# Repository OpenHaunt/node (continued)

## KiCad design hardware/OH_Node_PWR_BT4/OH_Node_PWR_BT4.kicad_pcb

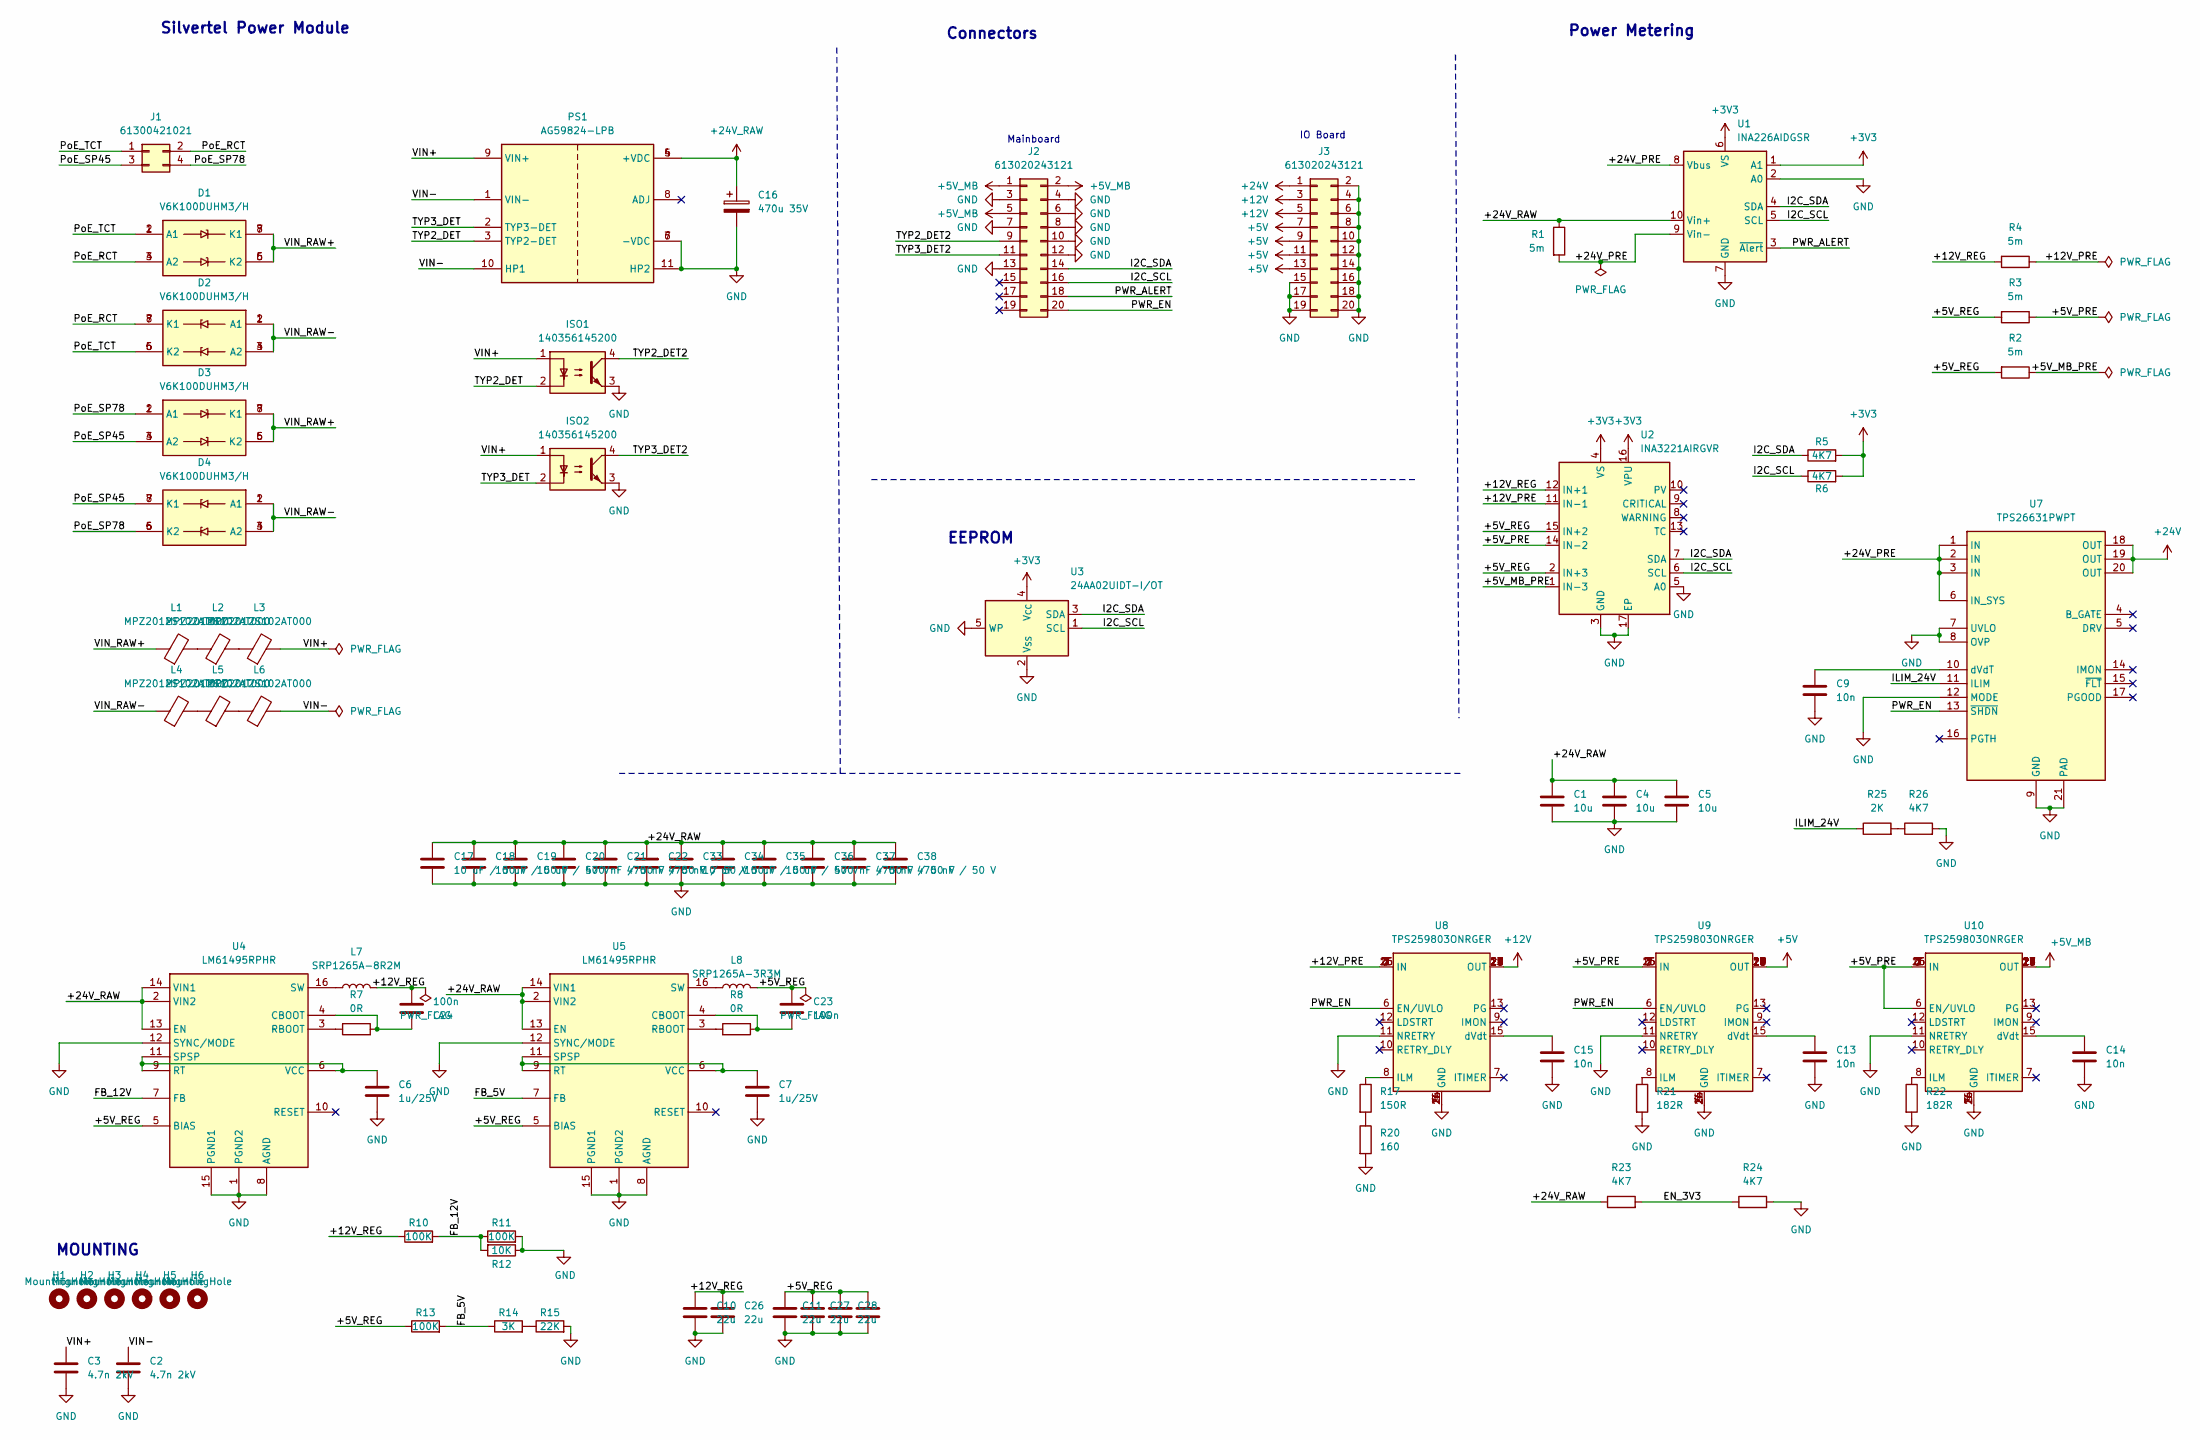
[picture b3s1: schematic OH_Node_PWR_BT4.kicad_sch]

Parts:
C1, C4, C5: 10u; C_0402_1005Metric; MPN GRM155R61A106ME11D
C2, C3: 4.7n 2kV; C_1812_4532Metric; MPN 885342211008
C6, C7: 1u/25V; C_0402_1005Metric; MPN CL05A105KA5NQNC
C9, C13, C14, C15: 10n; C_0402_1005Metric; MPN CL05B103KB5NNNC
C10, C11, C26, C27, C28, C29: 22u; C_1210_3225Metric; MPN GRM32ER71E226KE15L
C16: 470u 35V; CP_Elec_10x10.5; MPN EEH-ZU1V471P
C17, C18, C19, C33, C34, C35: 10 uF / 50 V; C_1210_3225Metric; MPN CC1210KKX7R9BB106
C20, C21, C22, C36, C37, C38: 470 nF / 50 V; C_0603_1608Metric; MPN C1608X7R1H474K080AC
C23, C24: 100n; C_0603_1608Metric; MPN CL10B104KB8NNNC
D1, D2, D3, D4: V6K100DUHM3/H; V6K100DUHM3H; Manufacturer_Part_Number V6K100DUHM3/H
H1, H2, H3, H4, H5, H6: MountingHole; MountingHole_2.7mm_M2.5_DIN965_Pad
ISO1, ISO2: 140356145200; WL-OCPT_SOP4; MPN 140356145200
J1: 61300421021; PinHeader_2x02_P2.54mm_Horizontal; MPN 61300421021
J2, J3: 613020243121; PinSocket_2x10_P2.54mm_Horizontal; MPN 613020243121
L1, L2, L3, L4, L5, L6: MPZ2012S102AT000; L_0805_2012Metric; MPN MPZ2012S102AT000
L7: SRP1265A-8R2M; Bourns_SRP1265A; MPN SRP1265A-8R2M
L8: SRP1265A-3R3M; Bourns_SRP1265A; MPN SRP1265A-3R3M
PS1: AG59824-LPB; AG59800-LPB; Manufacturer_Part_Number Ag5800
R1, R2, R3, R4: 5m; R_2512_6332Metric_Pad1.40x3.35mm_HandSolder; MPN PA2512FKM070R005E
R5, R6, R23, R24, R26: 4K7; R_0402_1005Metric; MPN RC0402JR-074K7L
R7, R8: 0R; R_0402_1005Metric; MPN RC0402JR-070RL
R10, R11, R13: 100K; R_0603_1608Metric; MPN RC0603JR-07100KL
R12: 10K; R_0402_1005Metric; MPN RC0402JR-0710KL
R14: 3K; R_0402_1005Metric; MPN RC0402JR-133KL
R15: 22K; R_0402_1005Metric; MPN RC0402JR-1322KL
R17: 150R; R_0402_1005Metric; MPN RC0402JR-07150RL
R20: 160; R_0402_1005Metric; MPN RC0402JR-07160RL
R21, R22: 182R; R_0402_1005Metric; MPN RC0402FR-07182RL
R25: 2K; R_0603_1608Metric; MPN RC0603FR-072KL
U1: INA226AIDGSR; MSOP-10_3x3mm_P0.5mm; MPN INA226AIDGSR
U2: INA3221AIRGVR; Texas_RGV0016A_VQFN-16-1EP_4x4mm_P0.65mm_EP2.1x2.1mm; MPN INA3221AIRGVR
U3: 24AA02UIDT-I/OT; SOT-23-5; MPN 24AA02UIDT-I/OT
U4, U5: LM61495RPHR; TI_LM61495RPHR; MPN LM61495RPHR
U7: TPS26631PWPT; HTSSOP-20-1EP_4.4x6.5mm_P0.65mm_EP2.74x3.86mm; MPN TPS26631PWPT
U8, U9, U10: TPS259803ONRGER; TI_TPS25980xx; MPN TPS259803ONRGER

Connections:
+3V3: R5.2, R6.2, U1.1 (A1), U1.6 (VS), U2.4 (VS), U2.16 (VPU), U3.4 (V_{CC})
+5V: J3.7, J3.9, J3.11, J3.13, U9.17 (OUT), U9.18 (OUT), U9.19 (OUT), U9.20 (OUT), U9.21 (OUT), U9.22 (OUT), U9.23 (OUT), U9.24 (OUT)
+5V_MB: J2.1, J2.2, J2.5, U10.17 (OUT), U10.18 (OUT), U10.19 (OUT), U10.20 (OUT), U10.21 (OUT), U10.22 (OUT), U10.23 (OUT), U10.24 (OUT)
+12V: J3.3, J3.5, U8.17 (OUT), U8.18 (OUT), U8.19 (OUT), U8.20 (OUT), U8.21 (OUT), U8.22 (OUT), U8.23 (OUT), U8.24 (OUT)
+24V: J3.1, U7.18 (OUT), U7.19 (OUT), U7.20 (OUT)
+24V_RAW: C1.1, C4.1, C5.1, C16.1, C17.1, C18.1, C19.1, C20.1, C21.1, C22.1, C33.1, C34.1, C35.1, C36.1, C37.1, C38.1, PS1.4 (+VDC), PS1.5 (+VDC), R1.1, R23.1, U1.10 (Vin+), U4.2 (VIN2), U4.13 (EN), U4.14 (VIN1), U5.2 (VIN2), U5.13 (EN), U5.14 (VIN1)
/+5V_MB_PRE: R2.1, U2.1 (IN-3)
/+5V_PRE: R3.1, U2.14 (IN-2), U9.1 (IN), U9.2 (IN), U9.3 (IN), U9.16 (IN), U9.25 (IN), U10.1 (IN), U10.2 (IN), U10.3 (IN), U10.6 (EN/UVLO), U10.16 (IN), U10.25 (IN)
/+5V_REG: C11.1, C23.1, C27.1, C28.1, C29.1, L8.2, R2.2, R3.2, R13.1, U2.2 (IN+3), U2.15 (IN+2), U4.5 (BIAS), U5.5 (BIAS)
/+12V_PRE: R4.1, U2.11 (IN-1), U8.1 (IN), U8.2 (IN), U8.3 (IN), U8.16 (IN), U8.25 (IN)
/+12V_REG: C10.1, C24.2, C26.1, L7.2, R4.2, R10.1, U2.12 (IN+1)
/+24V_PRE: R1.2, U1.8 (Vbus), U1.9 (Vin-), U7.1 (IN), U7.2 (IN), U7.3 (IN), U7.6 (IN_SYS)
/EN_3V3: R23.2, R24.1
/FB_5V: R13.2, R14.1, U5.7 (FB)
/FB_12V: R10.2, R11.1, R12.2, U4.7 (FB)
/I2C_SCL: J2.16, R6.1, U1.5 (SCL), U2.6 (SCL), U3.1 (SCL)
/I2C_SDA: J2.14, R5.1, U1.4 (SDA), U2.7 (SDA), U3.3 (SDA)
/ILIM_24V: R25.1, U7.11 (ILIM)
/PWR_ALERT: J2.18, U1.3 (~Alert)
/PWR_EN: J2.20, U7.13 (~SHDN), U8.6 (EN/UVLO), U9.6 (EN/UVLO)
/PoE_RCT: D1.3 (A2), D1.4 (A2), D2.7 (K1), D2.8 (K1), J1.2
/PoE_SP45: D3.3 (A2), D3.4 (A2), D4.7 (K1), D4.8 (K1), J1.3
/PoE_SP78: D3.1 (A1), D3.2 (A1), D4.5 (K2), D4.6 (K2), J1.4
/PoE_TCT: D1.1 (A1), D1.2 (A1), D2.5 (K2), D2.6 (K2), J1.1
/TYP2_DET: ISO1.2, PS1.3 (TYP2-DET)
/TYP2_DET2: ISO1.4, J2.9
/TYP3_DET: ISO2.2, PS1.2 (TYP3-DET)
/TYP3_DET2: ISO2.4, J2.11
/VIN+: C3.1, ISO1.1, ISO2.1, L3.2, PS1.9 (VIN+)
/VIN-: C2.1, L6.2, PS1.1 (VIN-), PS1.10 (HP1)
/VIN_RAW+: D1.5 (K2), D1.6 (K2), D1.7 (K1), D1.8 (K1), D3.5 (K2), D3.6 (K2), D3.7 (K1), D3.8 (K1), L1.1
/VIN_RAW-: D2.1 (A1), D2.2 (A1), D2.3 (A2), D2.4 (A2), D4.1 (A1), D4.2 (A1), D4.3 (A2), D4.4 (A2), L4.1
GND: C1.2, C2.2, C3.2, C4.2, C5.2, C6.2, C7.2, C9.2, C10.2, C11.2, C13.2, C14.2, C15.2, C16.2, C17.2, C18.2, C19.2, C20.2, C21.2, C22.2, C26.2, C27.2, C28.2, C29.2, C33.2, C34.2, C35.2, C36.2, C37.2, C38.2, ISO1.3, ISO2.3, J2.3, J2.4, J2.6, J2.7, J2.8, J2.10, J2.12, J2.13, J3.2, J3.4, J3.6, J3.8, J3.10, J3.12, J3.14, J3.15, J3.16, J3.17, J3.18, J3.19, J3.20, PS1.6 (-VDC), PS1.7 (-VDC), PS1.11 (HP2), R11.2, R12.1, R15.2, R20.2, R21.2, R22.2, R24.2, R26.2, U1.2 (A0), U1.7 (GND), U2.3 (GND), U2.5 (A0), U2.17 (EP), U3.2 (V_{SS}), U3.5 (WP), U4.1 (PGND2), U4.8 (AGND), U4.12 (SYNC/MODE), U4.15 (PGND1), U5.1 (PGND2), U5.8 (AGND), U5.12 (SYNC/MODE), U5.15 (PGND1), U7.7 (UVLO), U7.8 (OVP), U7.9 (GND), U7.12 (MODE), U7.21 (PAD), U8.4 (GND), U8.5 (GND), U8.11 (NRETRY), U8.14 (GND), U8.26 (GND), U9.4 (GND), U9.5 (GND), U9.11 (NRETRY), U9.14 (GND), U9.26 (GND), U10.4 (GND), U10.5 (GND), U10.11 (NRETRY), U10.14 (GND), U10.26 (GND)
unnamed: L1.2, L2.1
unnamed: L2.2, L3.1
unnamed: L4.2, L5.1
unnamed: L5.2, L6.1
unnamed: R14.2, R15.1
unnamed: R17.2, R20.1
unnamed: R25.2, R26.1
unnamed: C24.1, R7.2, U4.4 (CBOOT)
unnamed: R7.1, U4.3 (RBOOT)
unnamed: C6.1, U4.6 (VCC), U4.9 (RT), U4.11 (SPSP)
unnamed: L7.1, U4.16 (SW)
unnamed: C23.2, R8.1, U5.4 (CBOOT)
unnamed: R8.2, U5.3 (RBOOT)
unnamed: C7.1, U5.6 (VCC), U5.9 (RT), U5.11 (SPSP)
unnamed: L8.1, U5.16 (SW)
unnamed: C9.1, U7.10 (dVdT)
unnamed: R17.1, U8.8 (ILM)
unnamed: C15.1, U8.15 (dVdt)
unnamed: R21.1, U9.8 (ILM)
unnamed: C13.1, U9.15 (dVdt)
unnamed: R22.1, U10.8 (ILM)
unnamed: C14.1, U10.15 (dVdt)

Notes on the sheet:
Silvertel Power Module
Power Metering
Connectors
EEPROM
Mainboard
IO Board
MOUNTING

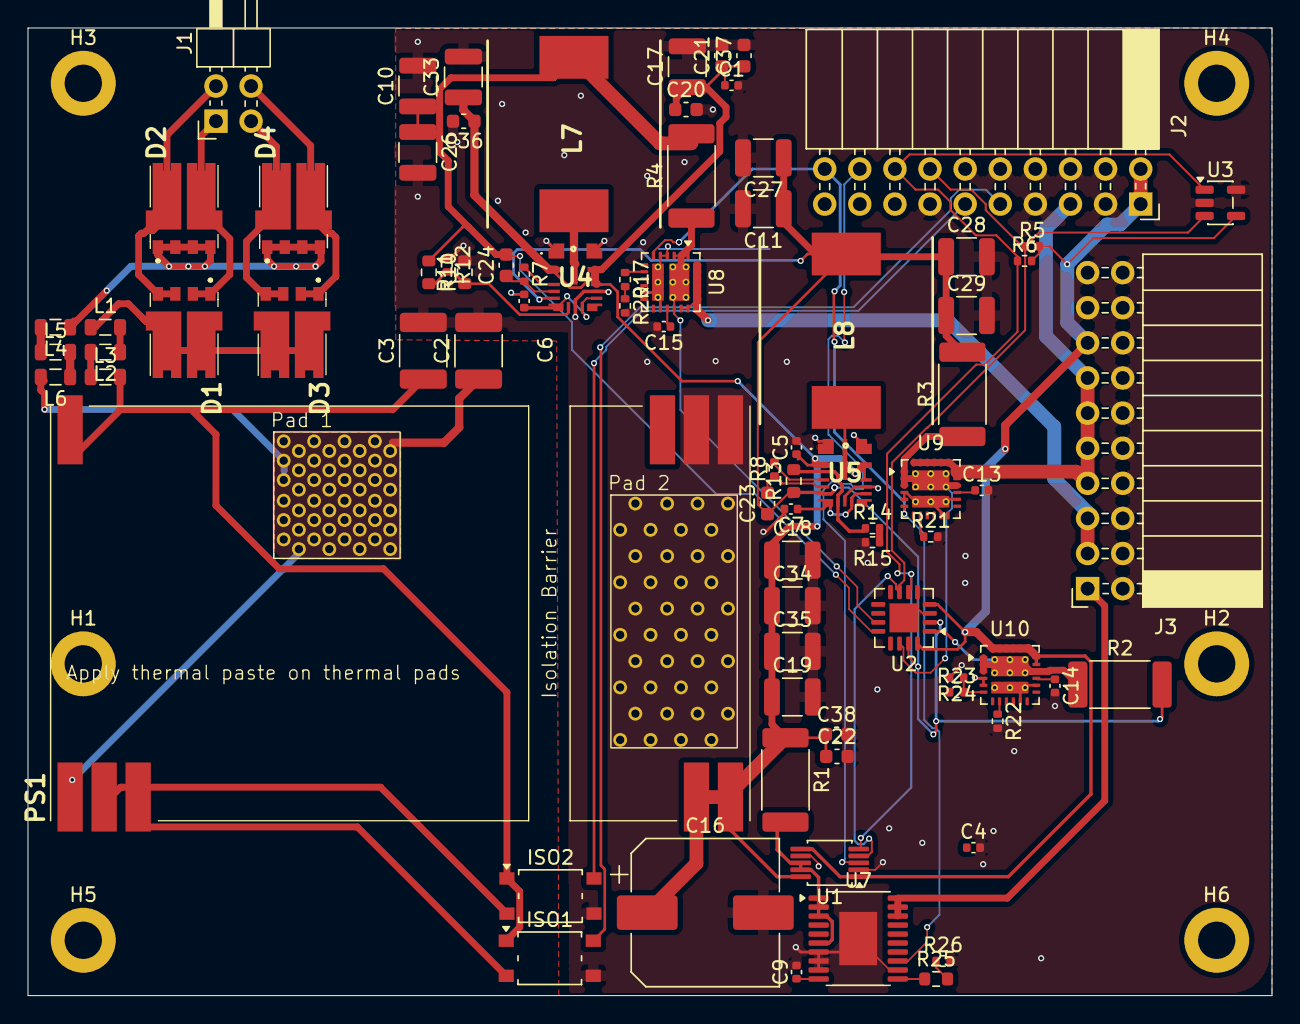
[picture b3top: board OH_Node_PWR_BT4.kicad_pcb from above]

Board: 4 copper layers, 90.0 x 70.0 mm, 87 parts (0 on the bottom side), 55 nets.

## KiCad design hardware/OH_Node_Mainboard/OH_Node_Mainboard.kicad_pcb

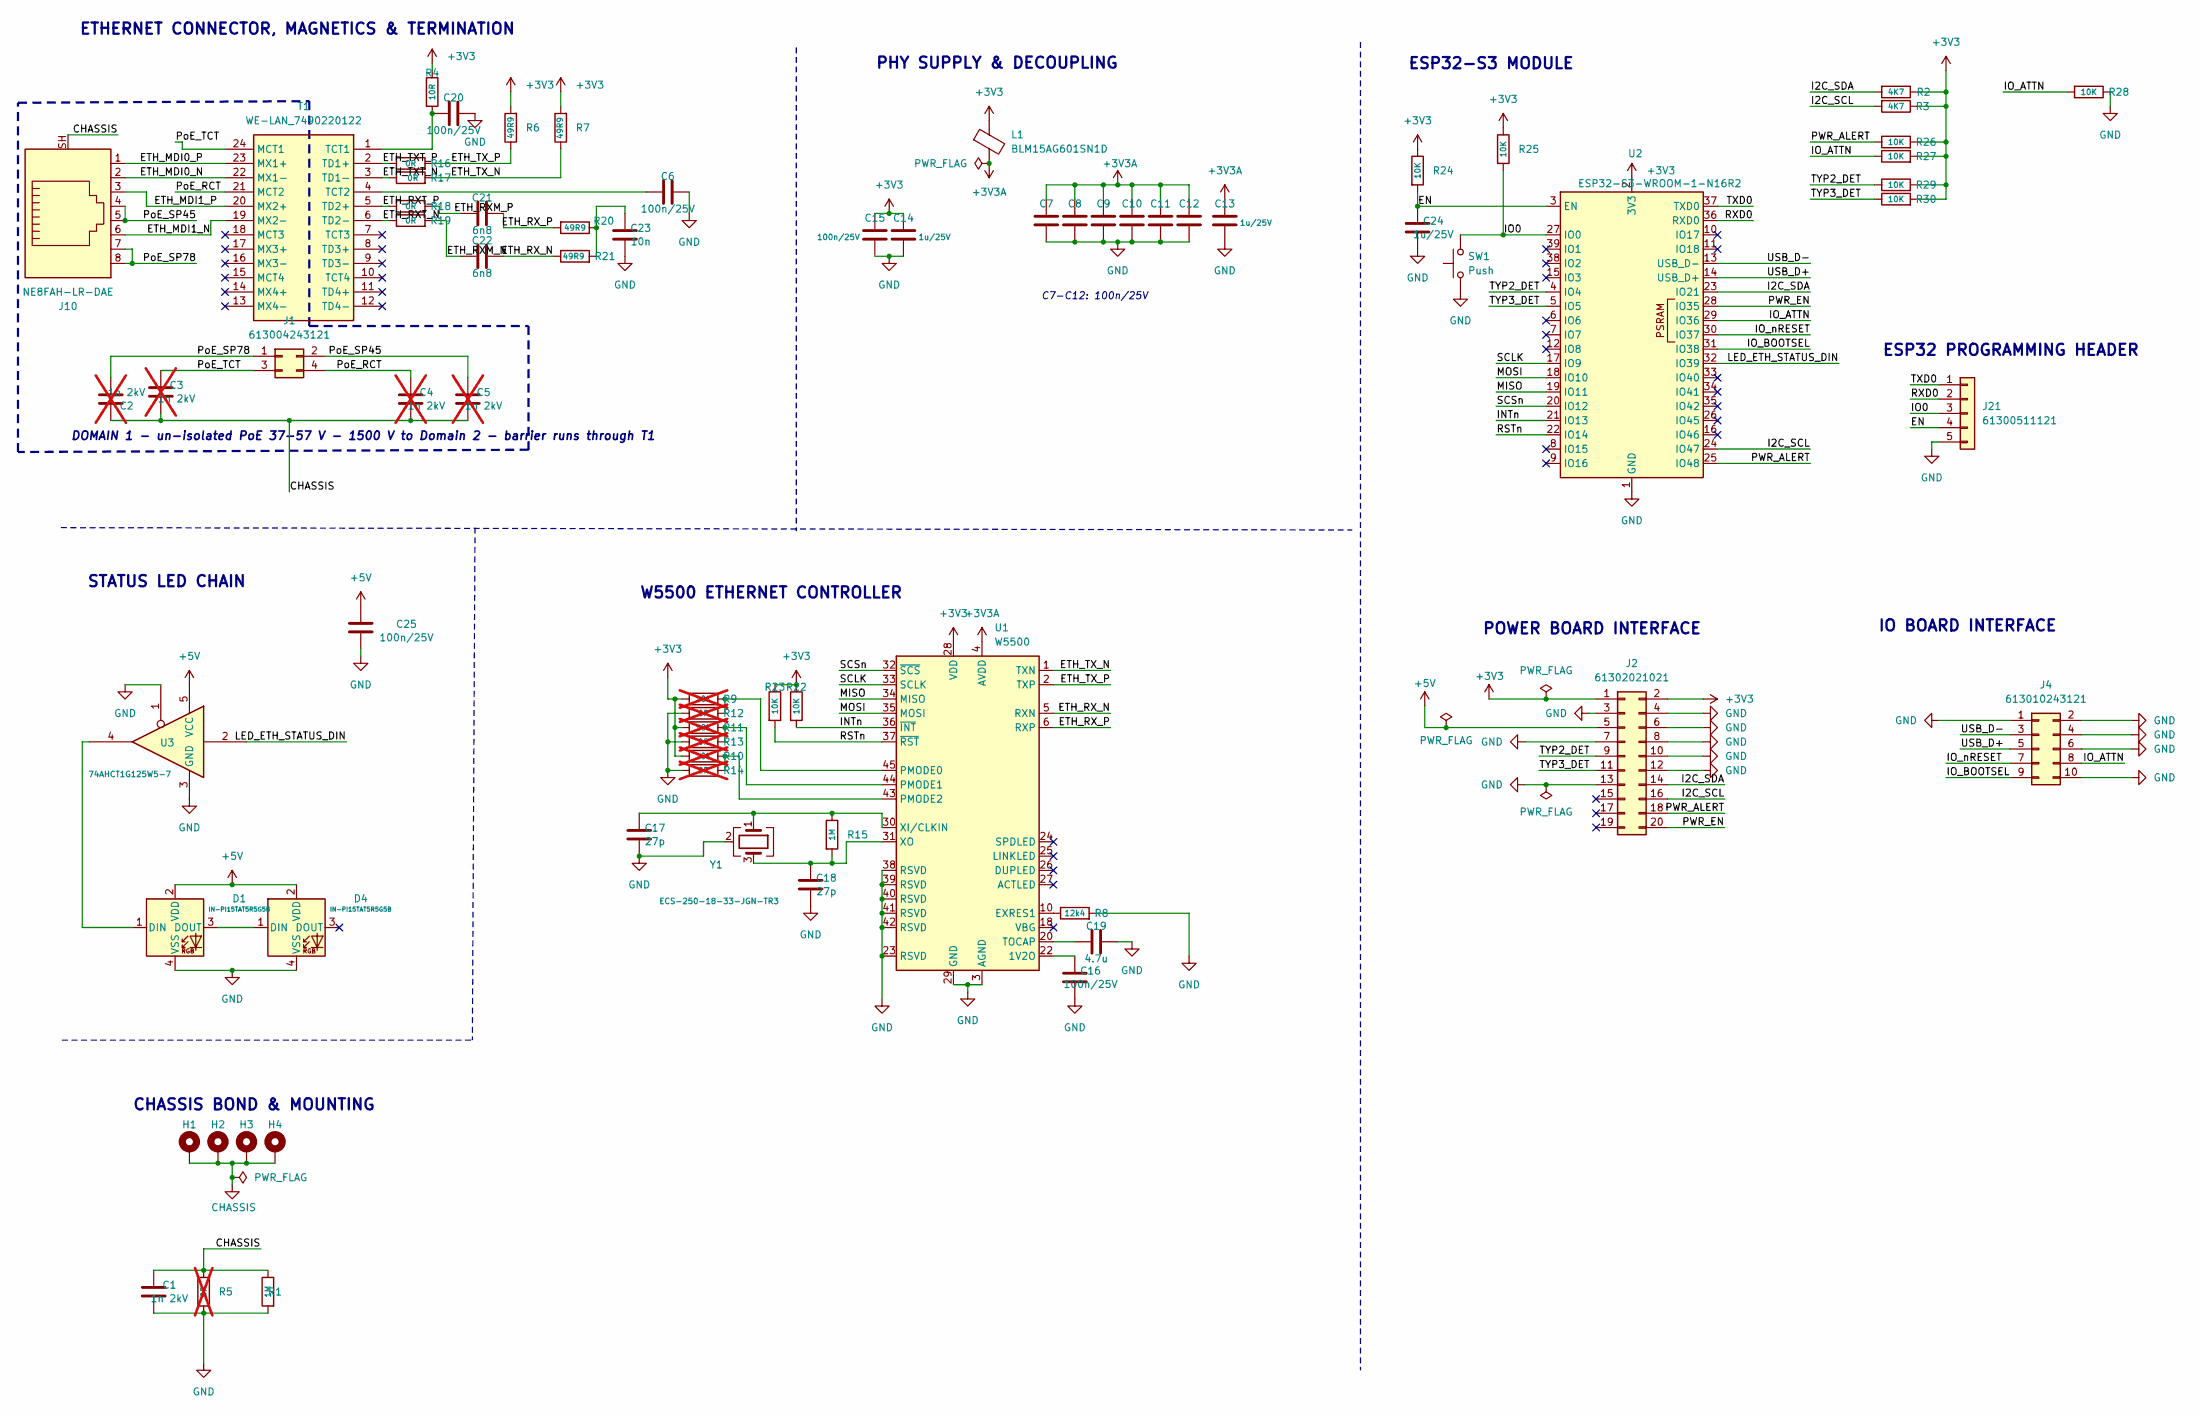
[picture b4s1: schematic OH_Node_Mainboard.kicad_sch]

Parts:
C1: 1n 2kV; C_1206_3216Metric; MPN 885342208024
C2, C3, C4, C5: 1n 2kV; C_1206_3216Metric; MPN 885342208024; not fitted
C6, C7, C8, C9, C10, C11, C12, C15, C16, C20, C25: 100n/25V; C_0402_1005Metric; MPN CL05A104KA5NNNC
C13, C14, C24: 1u/25V; C_0402_1005Metric; MPN CL05A105KA5NQNC
C17, C18: 27p; C_0402_1005Metric; MPN GRM1555C1H270JA01D
C19: 4.7u; C_0402_1005Metric; MPN CL21A475KLCLQNC
C21, C22: 6n8; C_0402_1005Metric; MPN CL05B682KB5NNNC
C23: 10n; C_0402_1005Metric; MPN CL05B103KB5NNNC
D1, D4: IN-PI15TAT5R5G5B; Inolux_IN-PI15TAT5R5G5B; MPN IN-PI15TAT5R5G5B
H1, H2, H3, H4: MountingHole_Pad; MountingHole_2.7mm_M2.5_DIN965_Pad
J1: 613004243121; PinSocket_2x02_P2.54mm_Horizontal; MPN 613004243121
J2: 61302021021; PinHeader_2x10_P2.54mm_Horizontal; MPN 61302021021
J4: 613010243121; PinSocket_2x05_P2.54mm_Horizontal; MPN 613010243121
J10: NE8FAH-LR-DAE; Neutrik_NE8FAH-LR-DAE; MPN NE8FAH-LR-DAE
J21: 61300511121; PinHeader_1x05_P2.54mm_Vertical; MPN 61300511121
L1: BLM15AG601SN1D; L_0402_1005Metric; MPN BLM15AG601SN1D
R1: 1M; R_0603_1608Metric; MPN RC0603JR-071ML
R2, R3: 4K7; R_0402_1005Metric; MPN RC0402JR-074K7L
R4: 10R; R_0402_1005Metric; MPN SR0402KR-0710RL
R5, R12, R13, R14: 0R; R_0402_1005Metric; MPN RC0402JR-070RL; not fitted
R6, R7, R20, R21: 49R9; R_0402_1005Metric; MPN RC0402FR-0749R9L
R8: 12k4; R_0402_1005Metric; MPN RC0402FR-0712K4L
R9, R10, R11: 10K; R_0402_1005Metric; MPN RC0402JR-0710KL; not fitted
R15: 1M; R_0402_1005Metric; MPN RC0402JR-071ML
R16, R17, R18, R19: 0R; R_0402_1005Metric; MPN RC0402JR-070RL
R22, R23, R24, R25, R26, R27, R28, R29, R30: 10K; R_0402_1005Metric; MPN RC0402JR-0710KL
SW1: Push; SW_Push_1P1T_NO_Vertical_Wuerth_434133025816; MPN 434133025816
T1: WE-LAN_7490220122; Manufacturer_Part_Number 7490220122
U1: W5500; LQFP-48_7x7mm_P0.5mm; MPN W5500
U2: ESP32-S3-WROOM-1-N16R2; Espressif_ESP32-S3-WROOM-1; MPN ESP32-S3-WROOM-1-N16R2
U3: 74AHCT1G125W5-7; SOT-353_SC-70-5; MPN 74AHCT1G125W5-7
Y1: ECS-250-18-33-JGN-TR3; Crystal_SMD_3225-4Pin_3.2x2.5mm; MPN ECS-250-18-33-JGN-TR3

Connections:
+3V3: C14.1, C15.1, J2.1, J2.2, L1.1, R2.1, R3.1, R4.1, R6.2, R7.2, R9.1, R10.1, R11.1, R22.1, R23.1, R24.1, R25.1, R26.2, R27.2, R29.2, R30.2, U1.28 (VDD), U2.2 (3V3)
+3V3A: C7.1, C8.1, C9.1, C10.1, C11.1, C12.1, C13.1, L1.2, U1.4 (AVDD), U1.8 (AVDD), U1.11 (AVDD), U1.15 (AVDD), U1.17 (AVDD), U1.21 (AVDD)
+5V: C25.1, D1.2 (VDD), D4.2 (VDD), J2.5, U3.5 (VCC)
/EN: C24.1, J21.4, R24.2, U2.3 (EN)
/ETH_MDI0_N: J10.2, T1.22 (MX1-)
/ETH_MDI0_P: J10.1, T1.23 (MX1+)
/ETH_MDI1_N: J10.6, T1.19 (MX2-)
/ETH_MDI1_P: J10.3, T1.20 (MX2+)
/ETH_RXM_N: C22.1, R19.2
/ETH_RXM_P: C21.1, R18.2
/ETH_RXT_N: R19.1, T1.6 (TD2-)
/ETH_RXT_P: R18.1, T1.5 (TD2+)
/ETH_RX_N: C22.2, R21.1, U1.5 (RXN)
/ETH_RX_P: C21.2, R20.2, U1.6 (RXP)
/ETH_TXT_N: R17.1, T1.3 (TD1-)
/ETH_TXT_P: R16.1, T1.2 (TD1+)
/ETH_TX_N: R7.1, R17.2, U1.1 (TXN)
/ETH_TX_P: R6.1, R16.2, U1.2 (TXP)
/I2C_SCL: J2.16, R3.2, U2.24 (IO47)
/I2C_SDA: J2.14, R2.2, U2.23 (IO21)
/INTn: R22.2, U1.36 (~INT), U2.21 (IO13)
/IO0: J21.3, R25.2, SW1.2, U2.27 (IO0)
/IO_ATTN: J4.8, R27.1, R28.2, U2.29 (IO36)
/IO_BOOTSEL: J4.9, U2.31 (IO38)
/IO_nRESET: J4.7, U2.30 (IO37)
/LED_ETH_STATUS_DIN: U2.32 (IO39), U3.2
/MISO: U1.34 (MISO), U2.19 (IO11)
/MOSI: U1.35 (MOSI), U2.18 (IO10)
/PWR_ALERT: J2.18, R26.1, U2.25 (IO48)
/PWR_EN: J2.20, U2.28 (IO35)
/PoE_RCT: C4.2, J1.4, T1.21 (MCT2)
/PoE_SP45: C5.2, J1.2, J10.4, J10.5
/PoE_SP78: C2.1, J1.1, J10.7, J10.8
/PoE_TCT: C3.2, J1.3, T1.24 (MCT1)
/RSTn: R23.2, U1.37 (~RST), U2.22 (IO14)
/RXD0: J21.2, U2.36 (RXD0)
/SCLK: U1.33 (SCLK), U2.17 (IO9)
/SCSn: U1.32 (~SCS), U2.20 (IO12)
/TXD0: J21.1, U2.37 (TXD0)
/TYP2_DET: J2.9, R29.1, U2.4 (IO4)
/TYP3_DET: J2.11, R30.1, U2.5 (IO5)
/USB_D+: J4.5, U2.14 (USB_D+)
/USB_D-: J4.3, U2.13 (USB_D-)
CHASSIS: C1.1, C2.2, C3.1, C4.1, C5.1, H1.1 (1_1), H2.1 (1_1), H3.1 (1_1), H4.1 (1_1), J10.SH, R1.1, R5.1
GND: C1.2, C6.2, C7.2, C8.2, C9.2, C10.2, C11.2, C12.2, C13.2, C14.2, C15.2, C16.2, C17.2, C18.2, C19.2, C20.2, C23.2, C24.2, C25.2, D1.4 (VSS), D4.4 (VSS), J2.3, J2.4, J2.6, J2.7, J2.8, J2.10, J2.12, J2.13, J4.1, J4.2, J4.4, J4.6, J4.10, J21.5, R1.2, R5.2, R8.2, R12.1, R13.1, R14.1, R28.1, SW1.1, U1.3 (AGND), U1.9 (AGND), U1.14 (AGND), U1.16 (AGND), U1.19 (AGND), U1.23 (RSVD), U1.29 (GND), U1.38 (RSVD), U1.39 (RSVD), U1.40 (RSVD), U1.41 (RSVD), U1.42 (RSVD), U1.48 (AGND), U2.1 (GND), U2.40 (GND), U2.41 (GND), U3.1, U3.3 (GND), Y1.2 (G), Y1.4 (G)
unnamed: C23.1, R20.1, R21.2
unnamed: D1.1 (DIN), U3.4
unnamed: D1.3 (DOUT), D4.1 (DIN)
unnamed: C20.1, R4.2, T1.1 (TCT1)
unnamed: C6.1, T1.4 (TCT2)
unnamed: C16.1, U1.22 (1V2O)
unnamed: R8.1, U1.10 (EXRES1)
unnamed: R9.2, R12.2, U1.45 (PMODE0)
unnamed: R11.2, R13.2, U1.44 (PMODE1)
unnamed: R10.2, R14.2, U1.43 (PMODE2)
unnamed: C19.1, U1.20 (TOCAP)
unnamed: C17.1, R15.1, U1.30 (XI/CLKIN), Y1.1
unnamed: C18.1, R15.2, U1.31 (XO), Y1.3

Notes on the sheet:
C7-C12: 100n/25V
IO BOARD INTERFACE
ETHERNET CONNECTOR, MAGNETICS & TERMINATION
ESP32 PROGRAMMING HEADER
POWER BOARD INTERFACE
ESP32-S3 MODULE
PHY SUPPLY & DECOUPLING
W5500 ETHERNET CONTROLLER
DOMAIN 1 - un-isolated PoE 37-57 V - 1500 V to Domain 2 - barrier runs through T1
CHASSIS BOND & MOUNTING
STATUS LED CHAIN

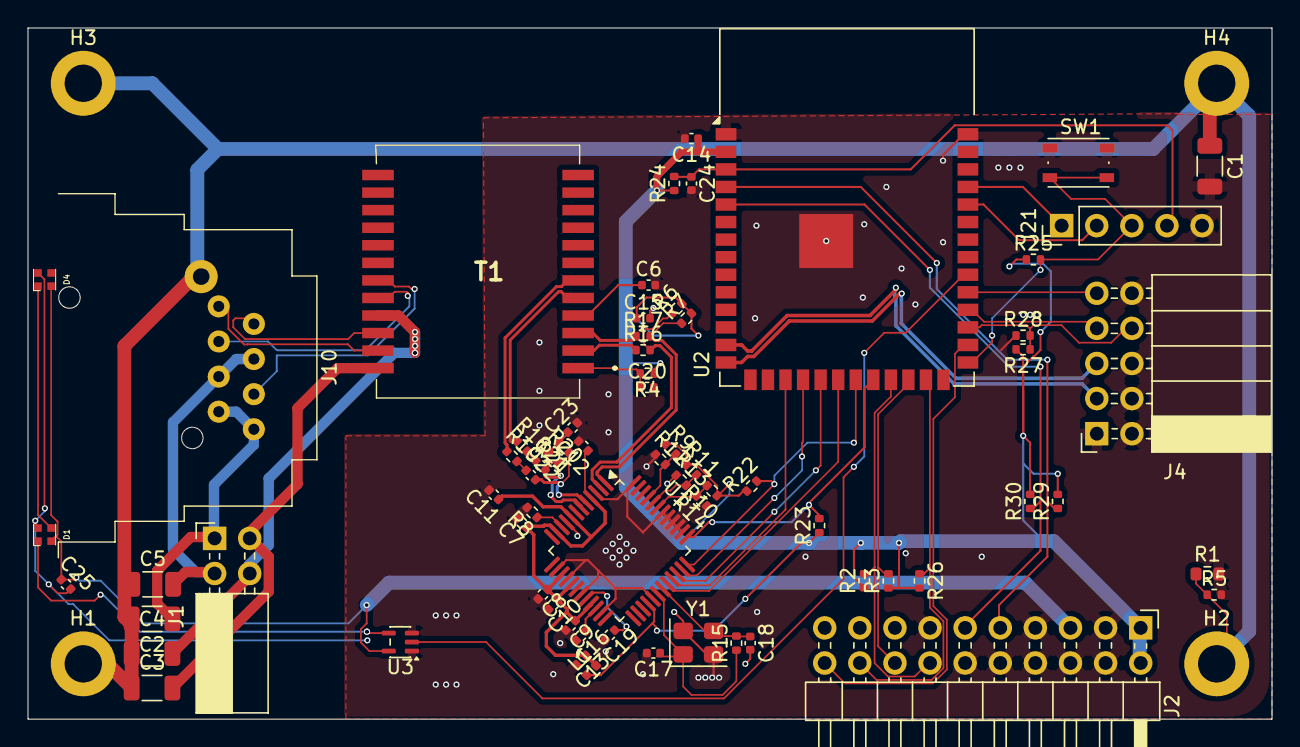
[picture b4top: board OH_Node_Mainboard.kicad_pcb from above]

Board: 4 copper layers, 90.0 x 50.0 mm, 73 parts (0 on the bottom side), 58 nets.

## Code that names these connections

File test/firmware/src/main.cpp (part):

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#include "rtp.h"
#include "sse.h"

constexpr uint8_t PIN_LED_R = 35;
constexpr uint8_t PIN_LED_Y = 36;

constexpr uint8_t PIN_ETH_SCLK = 9;
constexpr uint8_t PIN_ETH_MOSI = 10;
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constexpr uint8_t PIN_ETH_RST = 14;

// MAX98357A (U6): I2S in, ~SD_MODE driven directly by AMP_EN (3.3 V high = on, left slot only → mono mix)
constexpr uint8_t PIN_I2S_DIN = 40;
constexpr uint8_t PIN_I2S_BCLK = 41;
constexpr uint8_t PIN_I2S_LRCLK = 42;
constexpr uint8_t PIN_AMP_EN = 48;

// Motion detector signals: J8.3 → R34 → IO15, J10.3 → R36 → IO16
constexpr uint8_t PIN_PIR[PIR_COUNT] = {15, 16};
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      else r = true;
      if (eth == EthState::HwError) r = (tick / 2) % 2;
    }
    digitalWrite(PIN_LED_R, r);
    digitalWrite(PIN_LED_Y, y);
    vTaskDelay(pdMS_TO_TICKS(62));
  }
}
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    pinMode(pin, OUTPUT);
  }
  Serial.begin(115200);
  pinMode(PIN_LED_R, OUTPUT);
  pinMode(PIN_LED_Y, OUTPUT);
  xTaskCreate(ledTask, "led", 2048, nullptr, 1, nullptr);

  if (bootGuardMagic != BOOT_GUARD_MAGIC || esp_reset_reason() == ESP_RST_POWERON) {
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  ledBegin(PIN_LED_DATA);
  actionsBegin();

  if (!safeMode) audioBegin(PIN_I2S_BCLK, PIN_I2S_LRCLK, PIN_I2S_DIN, PIN_AMP_EN, true);
  loadAudioConfig();

  // Wi-Fi first: it brings up esp_netif and the default event loop, which Ethernet attaches to
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
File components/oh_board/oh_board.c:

#include "oh_board.h"

#include <stdlib.h>
#include <string.h>

#include "driver/gpio.h"
#include "sdkconfig.h"

static void parse_list(const char *text, int *out, int cap)
{
    for (int i = 0; i < cap; i++) {
        out[i] = -1;
    }
    int n = 0;
    const char *p = text;
    while (*p && n < cap) {
        char *end;
        long v = strtol(p, &end, 10);
        if (end == p) {
            break;
        }
        out[n++] = (int)v;
        p = end;
        while (*p == ',' || *p == ' ') {
            p++;
        }
    }
}

const oh_board_pins_t *oh_board_pins(void)
{
    static oh_board_pins_t pins;
    static bool ready;
    if (!ready) {
        pins.i2c_sda = CONFIG_OH_PIN_I2C_SDA;
        pins.i2c_scl = CONFIG_OH_PIN_I2C_SCL;
        pins.mod_int = CONFIG_OH_PIN_MOD_INT;
        pins.mod_fast0 = CONFIG_OH_PIN_MOD_FAST0;
        pins.mod_nreset = CONFIG_OH_PIN_MOD_NRESET;
        pins.mod_uart_tx = CONFIG_OH_PIN_MOD_UART_TX;
        pins.mod_uart_rx = CONFIG_OH_PIN_MOD_UART_RX;
        pins.mod_uart_de = CONFIG_OH_PIN_MOD_UART_DE;
        pins.button = CONFIG_OH_PIN_BUTTON;
        pins.button_active_low = CONFIG_OH_BUTTON_ACTIVE_LOW;
#ifdef CONFIG_OH_PIN_STATUS_LED
        pins.status_led = CONFIG_OH_PIN_STATUS_LED;
#else
        pins.status_led = -1;
#endif
        parse_list(CONFIG_OH_PRESET_INPUT_GPIOS, pins.preset_inputs, 8);
        parse_list(CONFIG_OH_PRESET_OUTPUT_GPIOS, pins.preset_outputs, 4);
#ifdef CONFIG_OH_BOARD_OH_NODE_V0
        parse_list(CONFIG_OH_PIN_RELAYS, pins.relays, 4);
        parse_list(CONFIG_OH_PIN_SENSORS, pins.sensors, 2);
#ifdef CONFIG_OH_SENSOR_CONTACT_READS_LOW
        pins.sensor_contact_low = true;
#endif
        parse_list(CONFIG_OH_PIN_STRIPS, pins.strips, 2);
        pins.strip_pixels = CONFIG_OH_STRIP_PIXELS;
        parse_list(CONFIG_OH_PIN_RELAY_LEDS, pins.relay_leds, 4);
        parse_list(CONFIG_OH_PIN_SENSOR_LEDS, pins.sensor_leds, 2);
        pins.i2s_dout = CONFIG_OH_PIN_I2S_DOUT;
        pins.i2s_bclk = CONFIG_OH_PIN_I2S_BCLK;
        pins.i2s_ws = CONFIG_OH_PIN_I2S_WS;
        pins.amp_en = CONFIG_OH_PIN_AMP_EN;
        pins.dac_mute = CONFIG_OH_PIN_DAC_MUTE;
#else
        parse_list("", pins.relays, 4);
        parse_list("", pins.sensors, 2);
        parse_list("", pins.strips, 2);
        parse_list("", pins.relay_leds, 4);
        parse_list("", pins.sensor_leds, 2);
        pins.i2s_dout = pins.i2s_bclk = pins.i2s_ws = -1;
        pins.amp_en = pins.dac_mute = -1;
#endif
        pins.error_led = CONFIG_OH_PIN_ERROR_LED;
        ready = true;
    }
    return &pins;
}

const char *oh_board_name(void)
{
    return CONFIG_OH_BOARD_NAME;
}

bool oh_board_has_display(void)
{
#ifdef CONFIG_OH_DISPLAY
    return true;
#else
    return false;
#endif
}

bool oh_board_has_ethernet(void)
{
#ifdef CONFIG_OH_TRANSPORT_ETH
    return true;
#else
    return false;
#endif
}

bool oh_board_has_builtin_io(void)
{
#ifdef CONFIG_OH_BOARD_OH_NODE_V0
    return true;
#else
    return false;
#endif
}

const char *oh_board_rev(void)
{
#if defined(CONFIG_OH_BOARD_OH_NODE_V0_1)
    return "0.1";
#elif defined(CONFIG_OH_BOARD_OH_NODE_V0_2)
    return "0.2";
#else
    return "";
#endif
}

void oh_board_init(void)
{
    const oh_board_pins_t *b = oh_board_pins();
    /* Audio stays silent until a driver claims it: the amplifier off and the
     * DAC muted. Both already default that way through their resistors; this
     * makes it so after a soft reset as well. */
    int quiet[] = {b->amp_en, b->dac_mute};
    for (size_t i = 0; i < sizeof(quiet) / sizeof(quiet[0]); i++) {
        if (quiet[i] >= 0) {
            gpio_config_t cfg = {.pin_bit_mask = 1ULL << quiet[i], .mode = GPIO_MODE_OUTPUT};
            gpio_config(&cfg);
            gpio_set_level(quiet[i], 0);
        }
    }
}
